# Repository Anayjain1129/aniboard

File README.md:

# Anay's Keyboard - Aniboard

Made by Anay

Features:

- EC11 Rotary Encoder - For Volume, Brightness etc
- TKL Layout minus (9 keys above the arrow keys)
- 0.91" OLED for Pictures, Current Playing Media etc.
- 78x keys
- Highway & Hack Club Branded Case
- Raspberry Pico
- Personalised layout
- KMK firmware

## Info

I made this keyboard since I wanted a keyboard with the Function keys and I use use two displays so it is not actually possible to use my laptop's keyboard all the time, I made this keyboard.

I think this i s perfect keyboard for me as it has a RE and a OLED display, which can help for like increasing hte volume or decreasing, and the display can help me with the things like the spotify stuff.

Oh and it also looks very nice in my eyes. Took me more than **40 hours** making the PCB, Case and researching for the BOM. I was really so much fun to make it.

## PCB

The PCB's size is 367.100mm x 133.750mm
| Schematic                     |
| ----------------------------- |
|  |

| Front                     |
| ------------------------- |
|  |

| Back                     |
| ------------------------ |
|  |

| 3D - Front                   |
| ---------------------------- |
|  |

| 3D - Back                   |
| --------------------------- |
|  |

## Case

I have made this case in Onshape.

there are two two parts for the case one is the top and another is the top.

# Top:

# Middle Plate:

# Bottom:

## 3D Render:

## Layout:

The Layout is a TKL (Tenkey-less) layout with some features like RE and OLED.

- removing Home, End etc island
- removing PrtSc etc island
- moving Fn key to bottom-left

## BOM

| Name                                                          | Qty | Final Price - INR (USD) | Link                                                                                                                        |
| ------------------------------------------------------------- | --- | ----------------------- | ----------------------------------------------------------------------------------------------------------                  |
| Gateron EF Grayish                                            | 80  | 1560 ($18.19)           | [here](https://neomacro.in/products/gateron-ef-grayish)                                                                     |
| Durock Smokey Screw-In Stabilizers V2 (4+1 w/ 6.25u spacebar) | 1   | 1299 ($15.14)           | [here](https://stackskb.com/store/durock-smokey-screw-in-stabilizers-v2/)                                                   |
| Cherry Profile PBT Keycaps                                    | 1   | 1595 ($18.6)            | [here](https://stackskb.com/store/veekos-gradient-keycaps-cherry-profile-135-keys)                                          |
| Diode 1N4148 Through - Hole                                   | 100 | 169 ($1.97)             | [here](https://amzn.in/d/j3eLvoh)                                                                                           |
| 0.91" OLED SSD1306                                            | 1   | 166 ($1.92)             | [here](https://amzn.in/d/3cISYEV)                                                                                           |
| EC11 Rotary Encoder                                           | 2   | 178 ($2.08)             | [here](https://amzn.in/d/hVRxzij)                                                                                           |
| M3 x 20mm Bolt                                                | 15  | 149 ($1.73)             | [here](https://amzn.in/d/8GRQWAB)                                                                                           |
| M3 Nuts                                                       | 8   | 100 ($1.16)             | [here](https://amzn.in/d/7UQtsm8)                                                                                           |
| M3 x 5mm Heatset Insert                                       | 25  | 179 ($2.09)             | [here](https://amzn.in/d/ixybuAc)                                                                                           |
| PCB - (Black Color)                                           | 5   | 4,923.83 ($56.87)       | [here](https://hc-cdn.hel1.your-objectstorage.com/s/v3/74e4c45af47010a7cc1c4b92517cf708e2c89ca2_swappy-20250622-232946.png) |
| Raspberry Pi Pico                                             | 1   | 449 ($5.19)             | [here](http://amazon.in/Raspberry-Pi-Headers-Soldered-Micro/dp/B08WPNM7JB/ref=sr_1_2?sr=8-2)                                |
| Soldering Iron                                                | 1   | 450 ($5.20)             | [here](https://www.amazon.in/INDITRUST-Soldering-adjustable-Temperature-Controlled/dp/B0DP7GJ5YK/ref=sr_1_9?sr=8-9)         |
| Top Case - 1 (Black "./production/CAD/top.step")              | 1   | Print Legion            |
| Bottom Case - 2 (Black "./production/CAD/bottom.step")        | 1   | Print Legion            |

## Total Pricing

The keyboard comes out to be 11217.83 INR ($129.23) When ordering all the parts I'm not including  the 3D parts because I will be getting them from Print Legion.

## Notes :-

I want all the two 3D-printed parts to be printed in black color. that includes: top.step, bottom.step .

The pricing might slightly vary due to flash sales, and dollar market trends.

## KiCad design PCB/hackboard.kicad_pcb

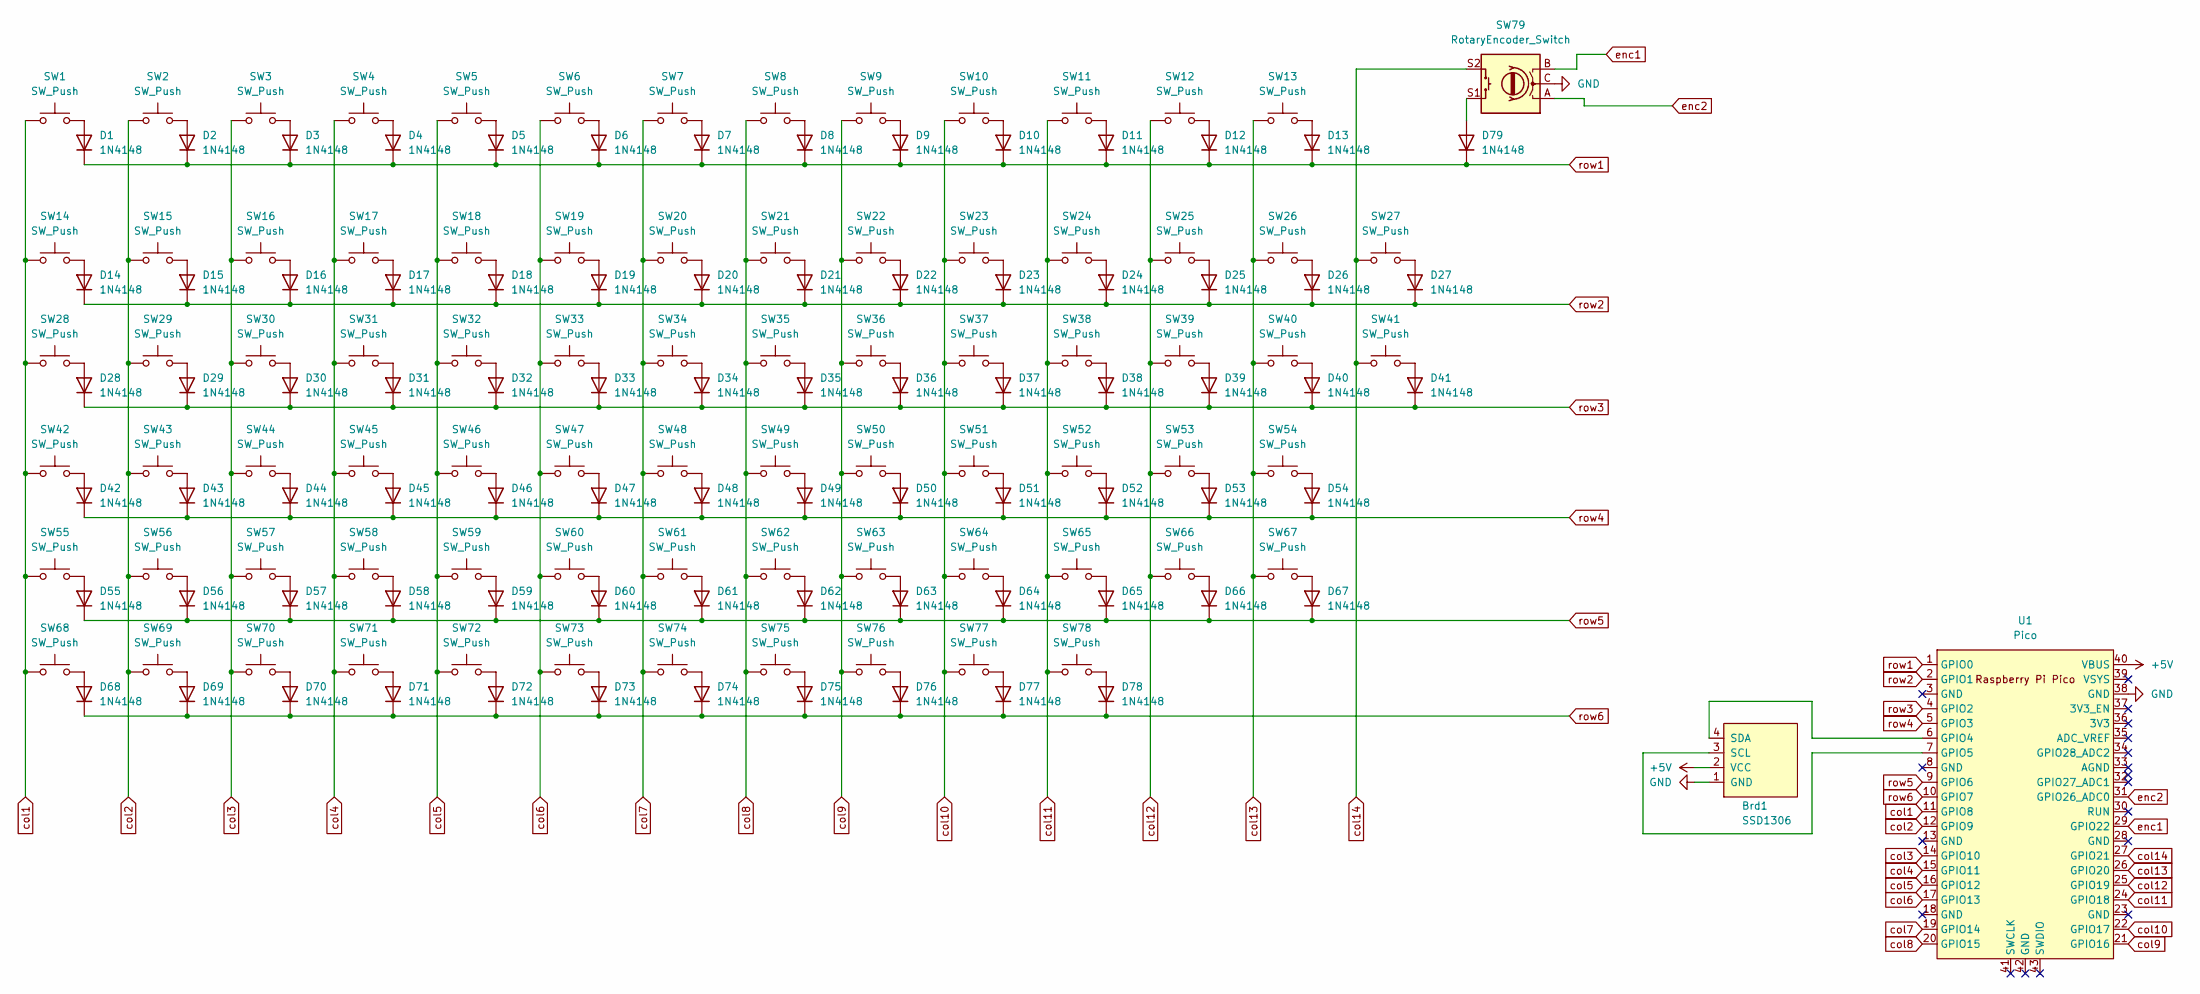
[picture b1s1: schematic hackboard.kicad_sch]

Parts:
Brd1: SSD1306; SSD1306-0.91-OLED-4pin-128x32
D1, D2, D3, D4, D5, D6, D7, D8, D9, D10, D11, D12, D13, D14, D15, D16, D17, D18, D19, D20, D21, D22, D23, D24, D25, D26, D27, D28, D29, D30, D31, D32, D33, D34, D35, D36, D37, D38, D39, D40, D41, D42, D43, D44, D45, D46, D47, D48, D49, D50, D51, D52, D53, D54, D55, D56, D57, D58, D59, D60, D61, D62, D63, D64, D65, D66, D67, D68, D69, D70, D71, D72, D73, D74, D75, D76, D77, D78, D79: 1N4148; D_DO-35_SOD27_P7.62mm_Horizontal
SW1, SW2, SW3, SW4, SW5, SW6, SW7, SW8, SW9, SW10, SW11, SW12, SW13, SW14, SW15, SW16, SW17, SW18, SW19, SW20, SW21, SW22, SW23, SW24, SW25, SW26, SW29, SW30, SW31, SW32, SW33, SW34, SW35, SW36, SW37, SW38, SW39, SW40, SW43, SW44, SW45, SW46, SW47, SW48, SW49, SW50, SW51, SW52, SW53, SW56, SW57, SW58, SW59, SW60, SW61, SW62, SW63, SW64, SW65, SW67, SW76, SW77, SW78: SW_Push; SW_Cherry_MX_1.00u_PCB
SW27: SW_Push; SW_Cherry_MX_2.00u_PCB
SW28, SW41: SW_Push; SW_Cherry_MX_1.50u_PCB
SW42: SW_Push; SW_Cherry_MX_1.75u_PCB
SW54, SW55: SW_Push; SW_Cherry_MX_2.25u_PCB
SW66: SW_Push; SW_Cherry_MX_2.75u_PCB
SW68, SW69, SW70, SW71, SW73, SW74, SW75: SW_Push; SW_Cherry_MX_1.25u_PCB
SW72: SW_Push; SW_Cherry_MX_6.25u_PCB
SW79: RotaryEncoder_Switch; RotaryEncoder_Alps_EC11E-Switch_Vertical_H20mm_CircularMoun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
U1: Pico; RPi_Pico_SMD_TH

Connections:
+5V: Brd1.2 (VCC), U1.40 (VBUS)
GND: Brd1.1 (GND), SW79.C, U1.38 (GND)
unnamed: Brd1.3 (SCL), U1.7 (GPIO5)
unnamed: Brd1.4 (SDA), U1.6 (GPIO4)
unnamed: D1.2 (A), SW1.2
unnamed: D2.2 (A), SW2.2
unnamed: D3.2 (A), SW3.2
unnamed: D4.2 (A), SW4.2
unnamed: D5.2 (A), SW5.2
unnamed: D6.2 (A), SW6.2
unnamed: D7.2 (A), SW7.2
unnamed: D8.2 (A), SW8.2
unnamed: D9.2 (A), SW9.2
unnamed: D10.2 (A), SW10.2
unnamed: D11.2 (A), SW11.2
unnamed: D12.2 (A), SW12.2
unnamed: D13.2 (A), SW13.2
unnamed: D14.2 (A), SW14.2
unnamed: D15.2 (A), SW15.2
unnamed: D16.2 (A), SW16.2
unnamed: D17.2 (A), SW17.2
unnamed: D18.2 (A), SW18.2
unnamed: D19.2 (A), SW19.2
unnamed: D20.2 (A), SW20.2
unnamed: D21.2 (A), SW21.2
unnamed: D22.2 (A), SW22.2
unnamed: D23.2 (A), SW23.2
unnamed: D24.2 (A), SW24.2
unnamed: D25.2 (A), SW25.2
unnamed: D26.2 (A), SW26.2
unnamed: D27.2 (A), SW27.2
unnamed: D28.2 (A), SW28.2
unnamed: D29.2 (A), SW29.2
unnamed: D30.2 (A), SW30.2
unnamed: D31.2 (A), SW31.2
unnamed: D32.2 (A), SW32.2
unnamed: D33.2 (A), SW33.2
unnamed: D34.2 (A), SW34.2
unnamed: D35.2 (A), SW35.2
unnamed: D36.2 (A), SW36.2
unnamed: D37.2 (A), SW37.2
unnamed: D38.2 (A), SW38.2
unnamed: D39.2 (A), SW39.2
unnamed: D40.2 (A), SW40.2
unnamed: D41.2 (A), SW41.2
unnamed: D42.2 (A), SW42.2
unnamed: D43.2 (A), SW43.2
unnamed: D44.2 (A), SW44.2
unnamed: D45.2 (A), SW45.2
unnamed: D46.2 (A), SW46.2
unnamed: D47.2 (A), SW47.2
unnamed: D48.2 (A), SW48.2
unnamed: D49.2 (A), SW49.2
unnamed: D50.2 (A), SW50.2
unnamed: D51.2 (A), SW51.2
unnamed: D52.2 (A), SW52.2
unnamed: D53.2 (A), SW53.2
unnamed: D54.2 (A), SW54.2
unnamed: D55.2 (A), SW55.2
unnamed: D56.2 (A), SW56.2
unnamed: D57.2 (A), SW57.2
unnamed: D58.2 (A), SW58.2
unnamed: D59.2 (A), SW59.2
unnamed: D60.2 (A), SW60.2
unnamed: D61.2 (A), SW61.2
unnamed: D62.2 (A), SW62.2
unnamed: D63.2 (A), SW63.2
unnamed: D64.2 (A), SW64.2
unnamed: D65.2 (A), SW65.2
unnamed: D66.2 (A), SW66.2
unnamed: D67.2 (A), SW67.2
unnamed: D68.2 (A), SW68.2
unnamed: D69.2 (A), SW69.2
unnamed: D70.2 (A), SW70.2
unnamed: D71.2 (A), SW71.2
unnamed: D72.2 (A), SW72.2
unnamed: D73.2 (A), SW73.2
unnamed: D74.2 (A), SW74.2
unnamed: D75.2 (A), SW75.2
unnamed: D76.2 (A), SW76.2
unnamed: D77.2 (A), SW77.2
unnamed: D78.2 (A), SW78.2
unnamed: D79.2 (A), SW79.S1
col1: SW1.1, SW14.1, SW28.1, SW42.1, SW55.1, SW68.1, U1.11 (GPIO8)
col2: SW2.1, SW15.1, SW29.1, SW43.1, SW56.1, SW69.1, U1.12 (GPIO9)
col3: SW3.1, SW16.1, SW30.1, SW44.1, SW57.1, SW70.1, U1.14 (GPIO10)
col4: SW4.1, SW17.1, SW31.1, SW45.1, SW58.1, SW71.1, U1.15 (GPIO11)
col5: SW5.1, SW18.1, SW32.1, SW46.1, SW59.1, SW72.1, U1.16 (GPIO12)
col6: SW6.1, SW19.1, SW33.1, SW47.1, SW60.1, SW73.1, U1.17 (GPIO13)
col7: SW7.1, SW20.1, SW34.1, SW48.1, SW61.1, SW74.1, U1.19 (GPIO14)
col8: SW8.1, SW21.1, SW35.1, SW49.1, SW62.1, SW75.1, U1.20 (GPIO15)
col9: SW9.1, SW22.1, SW36.1, SW50.1, SW63.1, SW76.1, U1.21 (GPIO16)
col10: SW10.1, SW23.1, SW37.1, SW51.1, SW64.1, SW77.1, U1.22 (GPIO17)
col11: SW11.1, SW24.1, SW38.1, SW52.1, SW65.1, SW78.1, U1.24 (GPIO18)
col12: SW12.1, SW25.1, SW39.1, SW53.1, SW66.1, U1.25 (GPIO19)
col13: SW13.1, SW26.1, SW40.1, SW54.1, SW67.1, U1.26 (GPIO20)
col14: SW27.1, SW41.1, SW79.S2, U1.27 (GPIO21)
enc1: SW79.B, U1.29 (GPIO22)
enc2: SW79.A, U1.31 (GPIO26_ADC0)
row1: D1.1 (K), D2.1 (K), D3.1 (K), D4.1 (K), D5.1 (K), D6.1 (K), D7.1 (K), D8.1 (K), D9.1 (K), D10.1 (K), D11.1 (K), D12.1 (K), D13.1 (K), D79.1 (K), U1.1 (GPIO0)
row2: D14.1 (K), D15.1 (K), D16.1 (K), D17.1 (K), D18.1 (K), D19.1 (K), D20.1 (K), D21.1 (K), D22.1 (K), D23.1 (K), D24.1 (K), D25.1 (K), D26.1 (K), D27.1 (K), U1.2 (GPIO1)
row3: D28.1 (K), D29.1 (K), D30.1 (K), D31.1 (K), D32.1 (K), D33.1 (K), D34.1 (K), D35.1 (K), D36.1 (K), D37.1 (K), D38.1 (K), D39.1 (K), D40.1 (K), D41.1 (K), U1.4 (GPIO2)
row4: D42.1 (K), D43.1 (K), D44.1 (K), D45.1 (K), D46.1 (K), D47.1 (K), D48.1 (K), D49.1 (K), D50.1 (K), D51.1 (K), D52.1 (K), D53.1 (K), D54.1 (K), U1.5 (GPIO3)
row5: D55.1 (K), D56.1 (K), D57.1 (K), D58.1 (K), D59.1 (K), D60.1 (K), D61.1 (K), D62.1 (K), D63.1 (K), D64.1 (K), D65.1 (K), D66.1 (K), D67.1 (K), U1.9 (GPIO6)
row6: D68.1 (K), D69.1 (K), D70.1 (K), D71.1 (K), D72.1 (K), D73.1 (K), D74.1 (K), D75.1 (K), D76.1 (K), D77.1 (K), D78.1 (K), U1.10 (GPIO7)

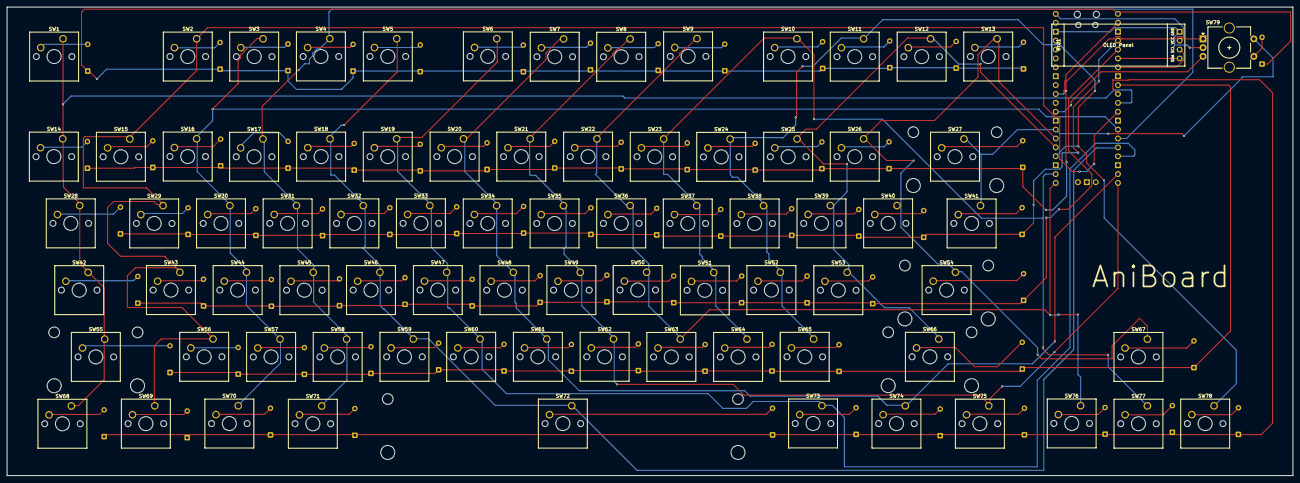
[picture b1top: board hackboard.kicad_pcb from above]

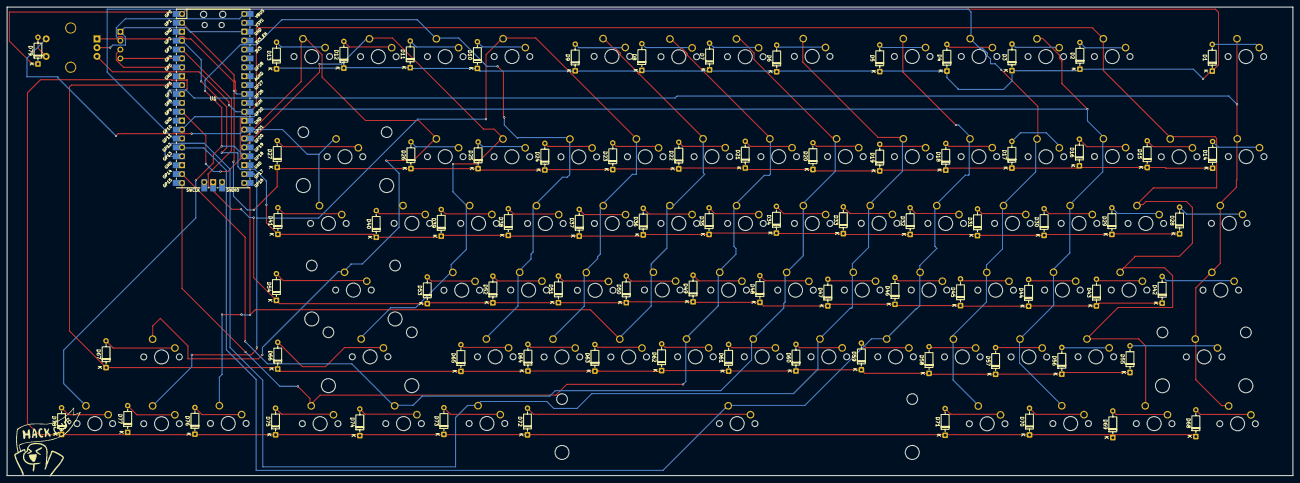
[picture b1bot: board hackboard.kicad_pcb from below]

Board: 2 copper layers, 367.1 x 133.7 mm, 161 parts (81 on the bottom side), 105 nets.

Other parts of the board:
Orpheus: LOGO

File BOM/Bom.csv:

Name,Qty,Final Price- INR (USD),Link
Gateron EF Grayish,80,1560 ($18.19),https://neomacro.in/products/gateron-ef-grayish
Durock Smokey Screw-In Stabilizers V2 (4+1 w/ 6.25u spacebar),1,1595 ($18.6),https://stackskb.com/store/durock-smokey-screw-in-stabilizers-v2/
Cherry Profile PBT Keycaps,1,1299 ($15.14),https://stackskb.com/store/veekos-gradient-keycaps-cherry-pr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
Diode 1N4148 Through – Hole,100,169 ($1.97),https://amzn.in/d/j3eLvoh
"0.91"" OLED SSD1306",1,166 ($1.92),https://amzn.in/d/3cISYEV
EC11 Rotary Encoder,2,178 ($2.08),https://amzn.in/d/hVRxzij
M3 x 20mm Bolt,15,149 ($1.73),https://amzn.in/d/8GRQWAB
M3 Nuts,8,100 ($1.16),https://amzn.in/d/7UQtsm8
M3 x 5mm Heatset Insert,25,179 ($2.09),https://amzn.in/d/ixybuAc
PCB - (Black Color),5,"4,923.83 ($56.87)",https://hc-cdn.hel1.your-objectstorage.com/s/v3/74e4c45af470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
Raspberry Pi Pico,1,449 ($5.19),http://amazon.in/Raspberry-Pi-Headers-Soldered-Micro/dp/B08W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
Soldering Iron,1,450 ($5.20),https://www.amazon.in/INDITRUST-Soldering-adjustable-Tempera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
"Top Case - 1 (Black ""./production/top.step"")",1,Print Legion,
"Bottom Case - 2 (Black ""./production/bottom.step"")",1,Print Legion,

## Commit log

2025-06-15 Rename JONURAL.md to JOURNAL.md
